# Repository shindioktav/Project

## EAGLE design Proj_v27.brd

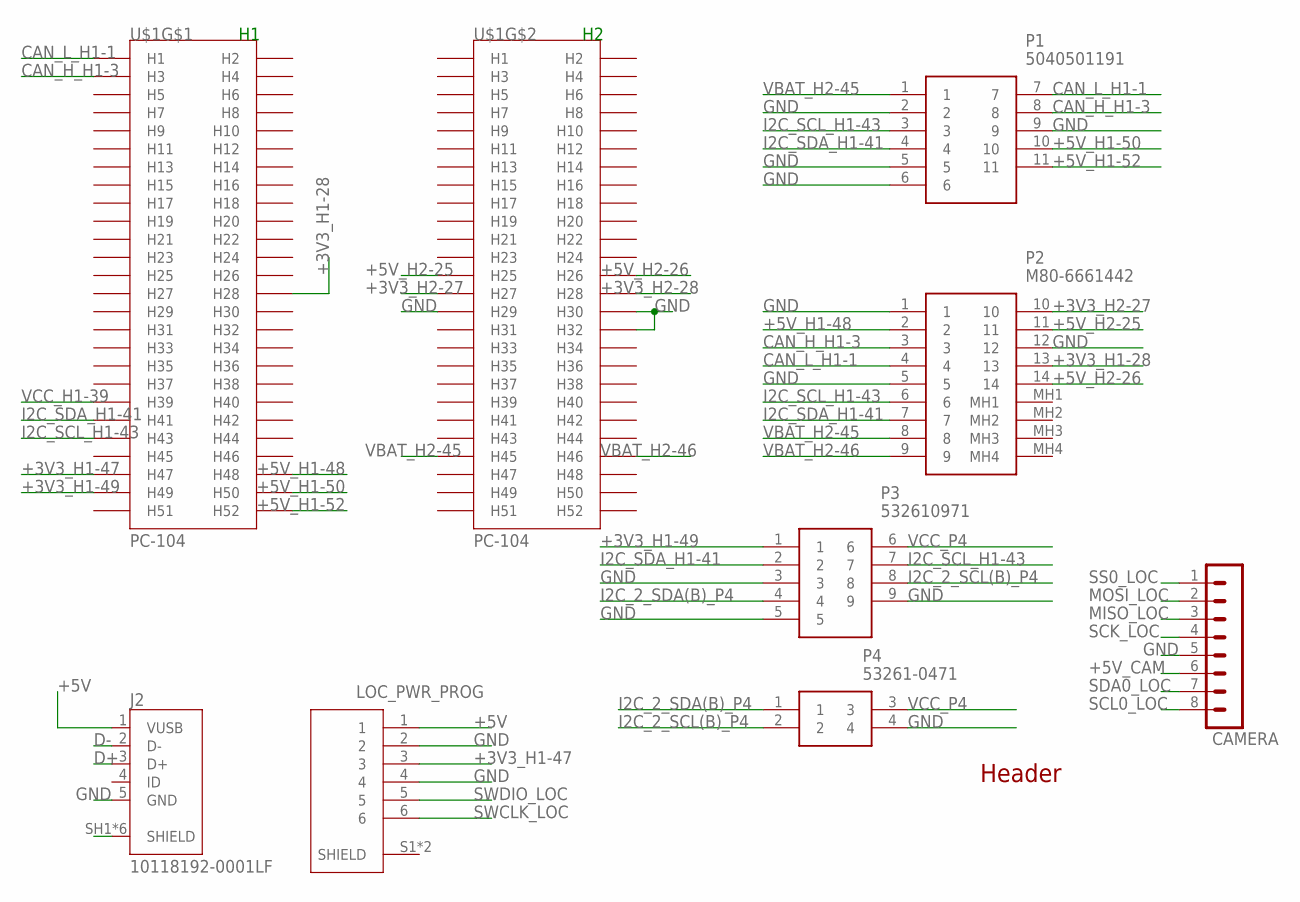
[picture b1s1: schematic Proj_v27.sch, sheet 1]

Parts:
CAMERA: MA08-1
J2: 10118192-0001LF; AMPHENOL_10118192-0001LF
LOC_PWR_PROG: 0532610671; MOLEX_0532610671
P1: 5040501191
P2: M80-6661442; M806661442
P3: 532610971
P4: 53261-0471
U$1: PC-104

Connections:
+3V3_H1-28: P2.13, U$1.P$28 (H28)
+3V3_H1-47: LOC_PWR_PROG.3, U$1.P$47 (H47); also elsewhere on the board
+3V3_H1-49: P3.1, U$1.P$49 (H49)
+3V3_H2-27: P2.10, U$1.P$79 (H27)
+3V3_H2-28: U$1.P$80 (H28)
+5V: J2.1 (VUSB), LOC_PWR_PROG.1; also elsewhere on the board
+5V_CAM: CAMERA.6; also elsewhere on the board
+5V_H1-48: P2.2, U$1.P$48 (H48)
+5V_H1-50: P1.10, U$1.P$50 (H50)
+5V_H1-52: P1.11, U$1.P$52 (H52)
+5V_H2-25: P2.11, U$1.P$77 (H25)
+5V_H2-26: P2.14, U$1.P$78 (H26)
CAN_H_H1-3: P1.8, P2.3, U$1.P$3 (H3)
CAN_L_H1-1: P1.7, P2.4, U$1.P$1 (H1)
D+: J2.3 (D+); also elsewhere on the board
D-: J2.2 (D-); also elsewhere on the board
GND: CAMERA.5, J2.5 (GND), J2.SH1 (SHIELD), J2.SH2 (SHIELD), J2.SH3 (SHIELD), J2.SH4 (SHIELD), J2.SH5 (SHIELD), J2.SH6 (SHIELD), LOC_PWR_PROG.2, LOC_PWR_PROG.4, P1.2, P1.5, P1.6, P1.9, P2.1, P2.5, P2.12, P3.3, P3.5, P3.9, P4.4, U$1.P$81 (H29), U$1.P$82 (H30), U$1.P$84 (H32); also elsewhere on the board
I2C_2_SCL(B)_P4: P3.8, P4.2
I2C_2_SDA(B)_P4: P3.4, P4.1
I2C_SCL_H1-43: P1.3, P2.6, P3.7, U$1.P$43 (H43); also elsewhere on the board
I2C_SDA_H1-41: P1.4, P2.7, P3.2, U$1.P$41 (H41); also elsewhere on the board
MISO_LOC: CAMERA.3; also elsewhere on the board
MOSI_LOC: CAMERA.2; also elsewhere on the board
SCK_LOC: CAMERA.4; also elsewhere on the board
SCL0_LOC: CAMERA.8; also elsewhere on the board
SDA0_LOC: CAMERA.7; also elsewhere on the board
SS0_LOC: CAMERA.1; also elsewhere on the board
SWCLK_LOC: LOC_PWR_PROG.6; also elsewhere on the board
SWDIO_LOC: LOC_PWR_PROG.5; also elsewhere on the board
VBAT_H2-45: P1.1, P2.8, U$1.P$97 (H45)
VBAT_H2-46: P2.9, U$1.P$98 (H46)
VCC_H1-39: U$1.P$39 (H39)
VCC_P4: P3.6, P4.3

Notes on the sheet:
Header

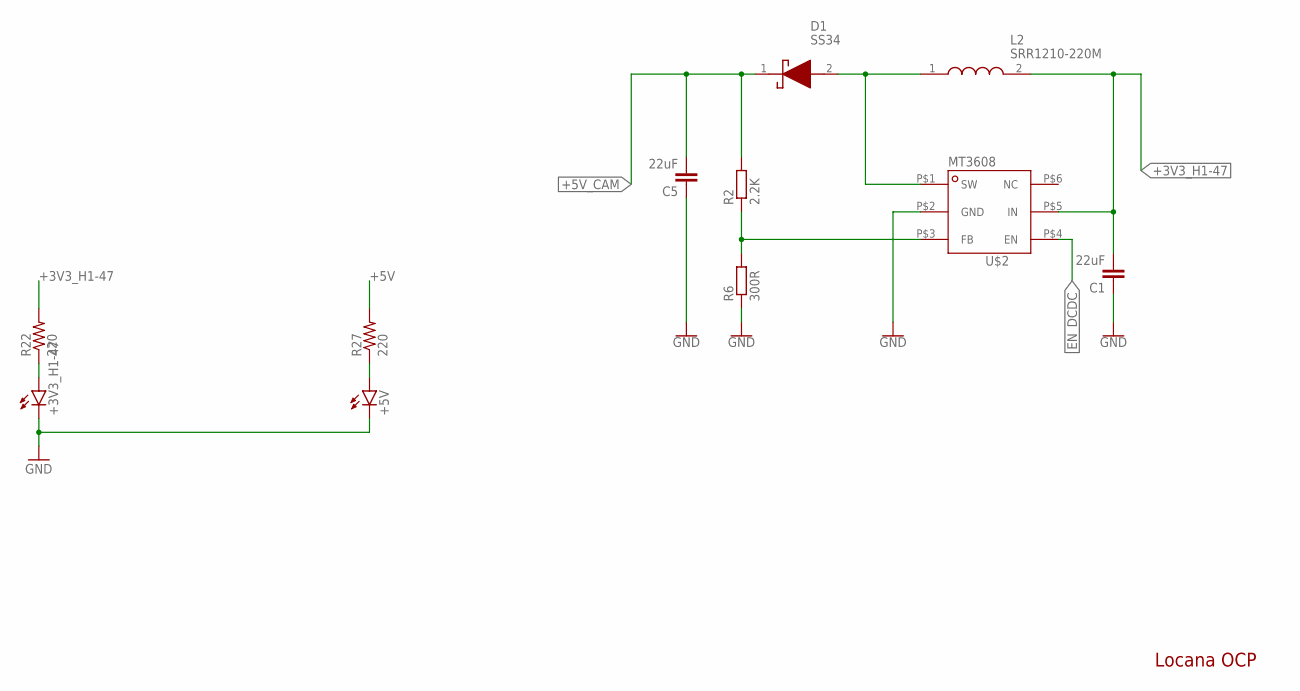
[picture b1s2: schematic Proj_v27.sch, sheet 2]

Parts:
+3V3_H1-47, +5V: LEDCHIP-LED0805; CHIP-LED0805
C1, C5: 22uF; C0805
D1: SS34; DIOM7959X262N
L2: SRR1210-220M; INDPM120120X1000N
R2: 2.2K; M0805
R6: 300R; M0805
R22, R27: 220; M0805
U$2: MT3608SOT23-6; SOT23-6

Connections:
+3V3_H1-47: C1.2, L2.2, R22.2, U$2.P$5 (IN); also elsewhere on the board
+5V: R27.2; also elsewhere on the board
+5V_CAM: C5.2, D1.1 (K), R2.2; also elsewhere on the board
EN_DCDC: U$2.P$4 (EN); also elsewhere on the board
GND: +3V3_H1-47.C, +5V.C, C1.1, C5.1, R6.1, U$2.P$2 (GND); also elsewhere on the board
unnamed: D1.2 (A), L2.1, U$2.P$1 (SW)
unnamed: R2.1, R6.2, U$2.P$3 (FB)
unnamed: +3V3_H1-47.A, R22.1
unnamed: +5V.A, R27.1

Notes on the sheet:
Locana OCP

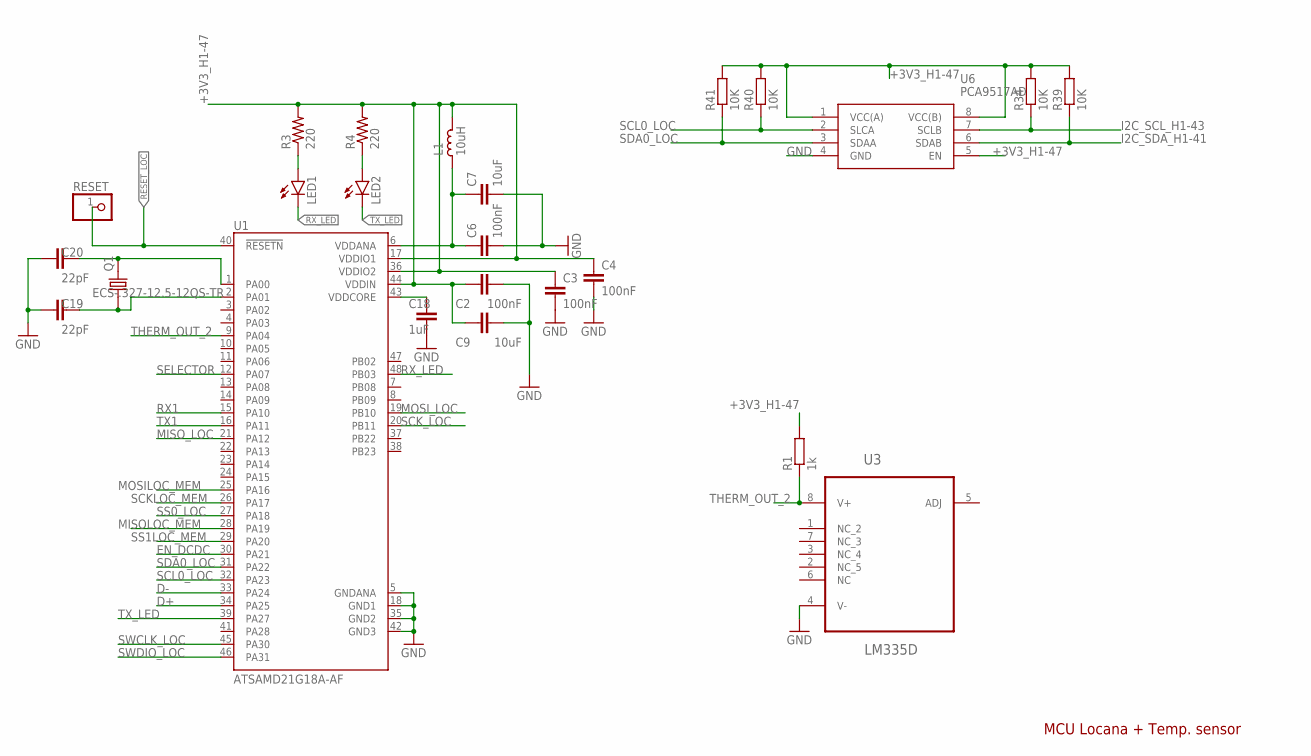
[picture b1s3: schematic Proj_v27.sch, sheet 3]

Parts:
C2, C3, C4, C6: 100nF; C0805K
C7, C9: 10uF; C0805K
C18: 1uF; C0805K
C19, C20: 22pF; C0805K
L1: 10uH; L0805
LED1, LED2: LEDCHIP-LED0805; CHIP-LED0805
Q1: ECS-.327-12.5-12QS-TR; XTAL_ECS-.327-12.5-12QS-TR
R1: 1k; M0805
R3, R4: 220; M0805
R34, R39, R40, R41: 10K; M0805
RESET: PINHD-1X1; 1X01
U1: ATSAMD21G18A-AF; QFP50P900X900X120-48N
U3: LM335D; SOIC127P600X175-8N
U6: PCA9517AD; SOIC127P600X175-8N

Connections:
+3V3_H1-47: C2.1, C3.1, C4.1, C9.1, L1.1, R1.2, R3.2, R4.2, R34.2, R39.2, R40.2, R41.2, U1.17 (VDDIO1), U1.36 (VDDIO2), U1.44 (VDDIN), U6.1 (VCC(A)), U6.5 (EN), U6.8 (VCC(B)); also elsewhere on the board
D+: U1.34 (PA25); also elsewhere on the board
D-: U1.33 (PA24); also elsewhere on the board
EN_DCDC: U1.30 (PA21); also elsewhere on the board
GND: C2.2, C3.2, C4.2, C6.2, C7.2, C9.2, C18.2, C19.1, C20.1, U1.5 (GNDANA), U1.18 (GND1), U1.35 (GND2), U1.42 (GND3), U3.4 (V-), U6.4 (GND); also elsewhere on the board
I2C_SCL_H1-43: R34.1, U6.7 (SCLB); also elsewhere on the board
I2C_SDA_H1-41: R39.1, U6.6 (SDAB); also elsewhere on the board
MISOLOC_MEM: U1.28 (PA19); also elsewhere on the board
MISO_LOC: U1.21 (PA12); also elsewhere on the board
MOSILOC_MEM: U1.25 (PA16); also elsewhere on the board
MOSI_LOC: U1.19 (PB10); also elsewhere on the board
unnamed: C20.2, Q1.2, U1.1 (PA00)
unnamed: C6.1, C7.1, L1.2, U1.6 (VDDANA)
unnamed: LED1.A, R3.1
unnamed: C18.1, U1.43 (VDDCORE)
unnamed: C19.2, Q1.1, U1.2 (PA01)
unnamed: LED2.A, R4.1
RESET_LOC: RESET.1, U1.40 (!RESETN)
RX1: U1.15 (PA10); also elsewhere on the board
RX_LED: LED1.C, U1.48 (PB03)
SCKLOC_MEM: U1.26 (PA17); also elsewhere on the board
SCK_LOC: U1.20 (PB11); also elsewhere on the board
SCL0_LOC: R40.1, U1.32 (PA23), U6.2 (SLCA); also elsewhere on the board
SDA0_LOC: R41.1, U1.31 (PA22), U6.3 (SDAA); also elsewhere on the board
SELECTOR: U1.12 (PA07); also elsewhere on the board
SS0_LOC: U1.27 (PA18); also elsewhere on the board
SS1LOC_MEM: U1.29 (PA20); also elsewhere on the board
SWCLK_LOC: U1.45 (PA30); also elsewhere on the board
SWDIO_LOC: U1.46 (PA31); also elsewhere on the board
THERM_OUT_2: R1.1, U1.9 (PA04), U3.8 (V+)
TX1: U1.16 (PA11); also elsewhere on the board
TX_LED: LED2.C, U1.39 (PA27)

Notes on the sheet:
MCU Locana + Temp. sensor

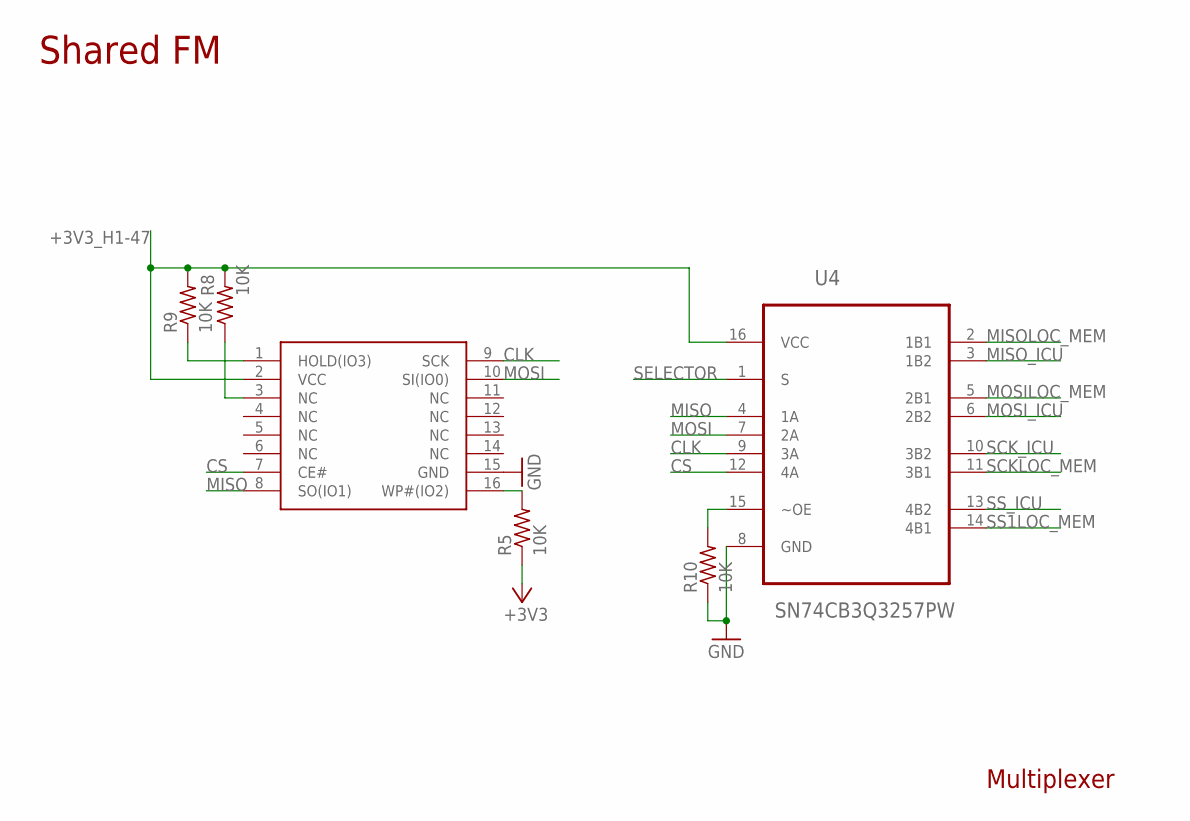
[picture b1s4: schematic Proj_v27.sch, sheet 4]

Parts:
LOC_MEM: SOIC127P600X175-16NSOIC-16YAS; SOIC127P1032X265-17T480X861N
R5, R8, R9, R10: 10K; M0805
U4: SN74CB3Q3257PW; SOP65P640X120-16N

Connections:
+3V3_H1-47: LOC_MEM.2 (VCC), R5.1, R8.2, R9.2, U4.16 (VCC); also elsewhere on the board
CLK: LOC_MEM.9 (SCK), U4.9 (3A)
CS: LOC_MEM.7 (CE#), U4.12 (4A)
GND: LOC_MEM.15 (GND), R10.1, U4.8 (GND); also elsewhere on the board
MISO: LOC_MEM.8 (SO(IO1)), U4.4 (1A)
MISOLOC_MEM: U4.2 (1B1); also elsewhere on the board
MISO_ICU: U4.3 (1B2); also elsewhere on the board
MOSI: LOC_MEM.10 (SI(IO0)), U4.7 (2A)
MOSILOC_MEM: U4.5 (2B1); also elsewhere on the board
MOSI_ICU: U4.6 (2B2); also elsewhere on the board
unnamed: LOC_MEM.16 (WP#(IO2)), R5.2
unnamed: LOC_MEM.1 (HOLD(IO3)), R9.1
unnamed: LOC_MEM.3 (NC), R8.1
unnamed: R10.2, U4.15 (~OE)
SCKLOC_MEM: U4.11 (3B1); also elsewhere on the board
SCK_ICU: U4.10 (3B2); also elsewhere on the board
SELECTOR: U4.1 (S); also elsewhere on the board
SS1LOC_MEM: U4.14 (4B1); also elsewhere on the board
SS_ICU: U4.13 (4B2); also elsewhere on the board

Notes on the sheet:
Shared FM
Multiplexer

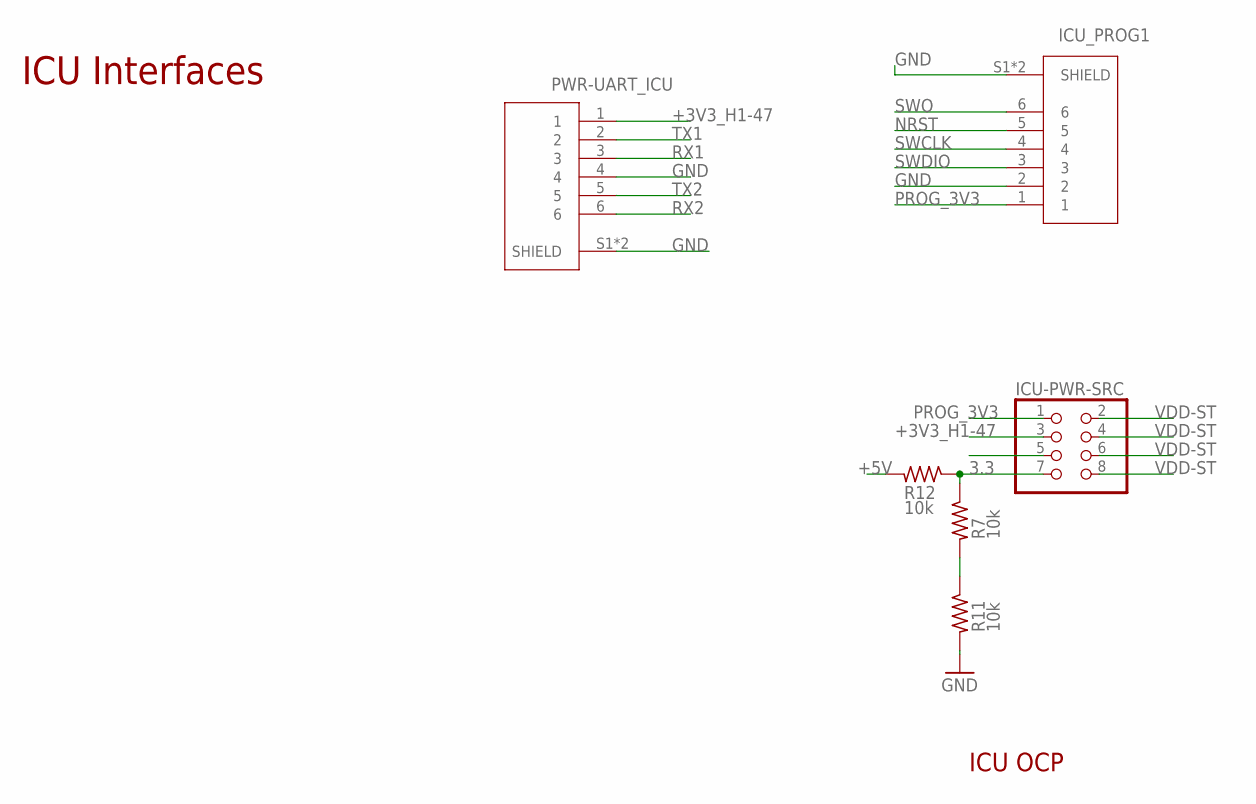
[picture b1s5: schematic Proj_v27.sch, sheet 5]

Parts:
ICU-PWR-SRC: PINHD-2X4; 2X04
ICU_PROG1: 0532610671; MOLEX_0532610671
PWR-UART_ICU: 0532610671; MOLEX_0532610671
R7, R11, R12: 10k; R0805

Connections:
3.3: ICU-PWR-SRC.7, R7.1, R12.1
+3V3_H1-47: ICU-PWR-SRC.3, PWR-UART_ICU.1; also elsewhere on the board
+5V: R12.2; also elsewhere on the board
GND: ICU_PROG1.2, ICU_PROG1.S1 (SHIELD), ICU_PROG1.S2 (SHIELD), PWR-UART_ICU.4, PWR-UART_ICU.S1 (SHIELD), PWR-UART_ICU.S2 (SHIELD), R11.2; also elsewhere on the board
unnamed: R7.2, R11.1
NRST: ICU_PROG1.5; also elsewhere on the board
PROG_3V3: ICU-PWR-SRC.1, ICU_PROG1.1
RX1: PWR-UART_ICU.3; also elsewhere on the board
RX2: PWR-UART_ICU.6; also elsewhere on the board
SWCLK: ICU_PROG1.4; also elsewhere on the board
SWDIO: ICU_PROG1.3; also elsewhere on the board
SWO: ICU_PROG1.6; also elsewhere on the board
TX1: PWR-UART_ICU.2; also elsewhere on the board
TX2: PWR-UART_ICU.5; also elsewhere on the board
VDD-ST: ICU-PWR-SRC.2, ICU-PWR-SRC.4, ICU-PWR-SRC.6, ICU-PWR-SRC.8; also elsewhere on the board

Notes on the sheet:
ICU Interfaces
ICU OCP

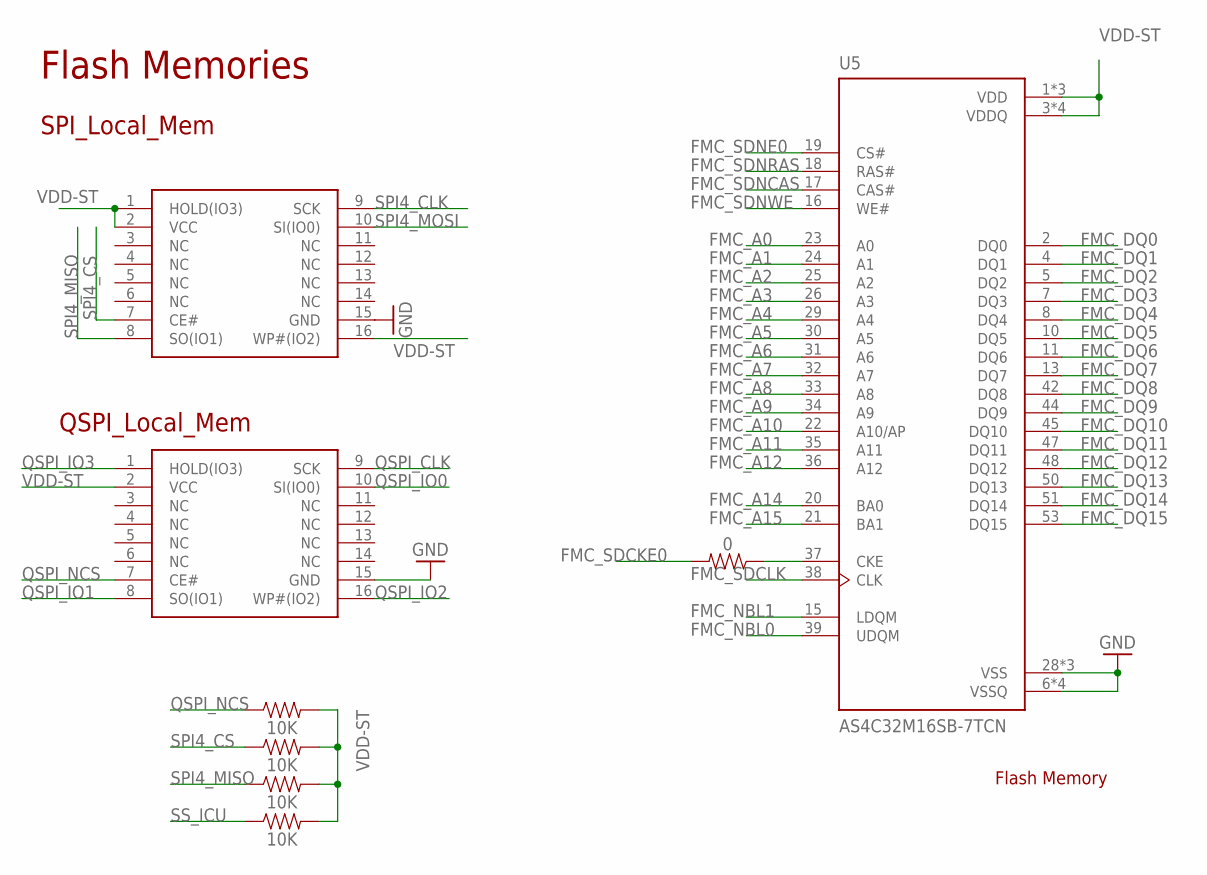
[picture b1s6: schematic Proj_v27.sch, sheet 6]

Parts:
LOCAL_MEM: SOIC127P600X175-16NSOIC-16YAS; SOIC127P1032X265-17T480X861N
QSPI_MEM: SOIC127P600X175-16NSOIC-16YAS; SOIC127P1032X265-17T480X861N
R25: 0; R0805
R76, R77, R78, R79: 10K; R0805
U5: AS4C32M16SB-7TCN; SOP80P1176X120-54N

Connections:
FMC_A0: U5.23 (A0); also elsewhere on the board
FMC_A1: U5.24 (A1); also elsewhere on the board
FMC_A2: U5.25 (A2); also elsewhere on the board
FMC_A3: U5.26 (A3); also elsewhere on the board
FMC_A4: U5.29 (A4); also elsewhere on the board
FMC_A5: U5.30 (A5); also elsewhere on the board
FMC_A6: U5.31 (A6); also elsewhere on the board
FMC_A7: U5.32 (A7); also elsewhere on the board
FMC_A8: U5.33 (A8); also elsewhere on the board
FMC_A9: U5.34 (A9); also elsewhere on the board
FMC_A10: U5.22 (A10/AP); also elsewhere on the board
FMC_A11: U5.35 (A11); also elsewhere on the board
FMC_A12: U5.36 (A12); also elsewhere on the board
FMC_A14: U5.20 (BA0); also elsewhere on the board
FMC_A15: U5.21 (BA1); also elsewhere on the board
FMC_DQ0: U5.2 (DQ0); also elsewhere on the board
FMC_DQ1: U5.4 (DQ1); also elsewhere on the board
FMC_DQ2: U5.5 (DQ2); also elsewhere on the board
FMC_DQ3: U5.7 (DQ3); also elsewhere on the board
FMC_DQ4: U5.8 (DQ4); also elsewhere on the board
FMC_DQ5: U5.10 (DQ5); also elsewhere on the board
FMC_DQ6: U5.11 (DQ6); also elsewhere on the board
FMC_DQ7: U5.13 (DQ7); also elsewhere on the board
FMC_DQ8: U5.42 (DQ8); also elsewhere on the board
FMC_DQ9: U5.44 (DQ9); also elsewhere on the board
FMC_DQ10: U5.45 (DQ10); also elsewhere on the board
FMC_DQ11: U5.47 (DQ11); also elsewhere on the board
FMC_DQ12: U5.48 (DQ12); also elsewhere on the board
FMC_DQ13: U5.50 (DQ13); also elsewhere on the board
FMC_DQ14: U5.51 (DQ14); also elsewhere on the board
FMC_DQ15: U5.53 (DQ15); also elsewhere on the board
FMC_NBL0: U5.39 (UDQM); also elsewhere on the board
FMC_NBL1: U5.15 (LDQM); also elsewhere on the board
FMC_SDCKE0: R25.1, R25.2, U5.37 (CKE); also elsewhere on the board
FMC_SDCLK: U5.38 (CLK); also elsewhere on the board
FMC_SDNCAS: U5.17 (CAS#); also elsewhere on the board
FMC_SDNE0: U5.19 (CS#); also elsewhere on the board
FMC_SDNRAS: U5.18 (RAS#); also elsewhere on the board
FMC_SDNWE: U5.16 (WE#); also elsewhere on the board
GND: LOCAL_MEM.15 (GND), QSPI_MEM.15 (GND), U5.6 (VSSQ), U5.12 (VSSQ), U5.28 (VSS), U5.41 (VSS), U5.46 (VSSQ), U5.52 (VSSQ), U5.54 (VSS); also elsewhere on the board
QSPI_CLK: QSPI_MEM.9 (SCK); also elsewhere on the board
QSPI_IO0: QSPI_MEM.10 (SI(IO0)); also elsewhere on the board
QSPI_IO1: QSPI_MEM.8 (SO(IO1)); also elsewhere on the board
QSPI_IO2: QSPI_MEM.16 (WP#(IO2)); also elsewhere on the board
QSPI_IO3: QSPI_MEM.1 (HOLD(IO3)); also elsewhere on the board
QSPI_NCS: QSPI_MEM.7 (CE#), R79.1; also elsewhere on the board
SPI4_CLK: LOCAL_MEM.9 (SCK); also elsewhere on the board
SPI4_CS: LOCAL_MEM.7 (CE#), R78.1; also elsewhere on the board
SPI4_MISO: LOCAL_MEM.8 (SO(IO1)), R77.1; also elsewhere on the board
SPI4_MOSI: LOCAL_MEM.10 (SI(IO0)); also elsewhere on the board
SS_ICU: R76.1; also elsewhere on the board
VDD-ST: LOCAL_MEM.1 (HOLD(IO3)), LOCAL_MEM.2 (VCC), LOCAL_MEM.16 (WP#(IO2)), QSPI_MEM.2 (VCC), R76.2, R77.2, R78.2, R79.2, U5.1 (VDD), U5.3 (VDDQ), U5.9 (VDDQ), U5.14 (VDD), U5.27 (VDD), U5.43 (VDDQ), U5.49 (VDDQ); also elsewhere on the board

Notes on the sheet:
Flash Memories
SPI_Local_Mem
Flash Memory
QSPI_Local_Mem

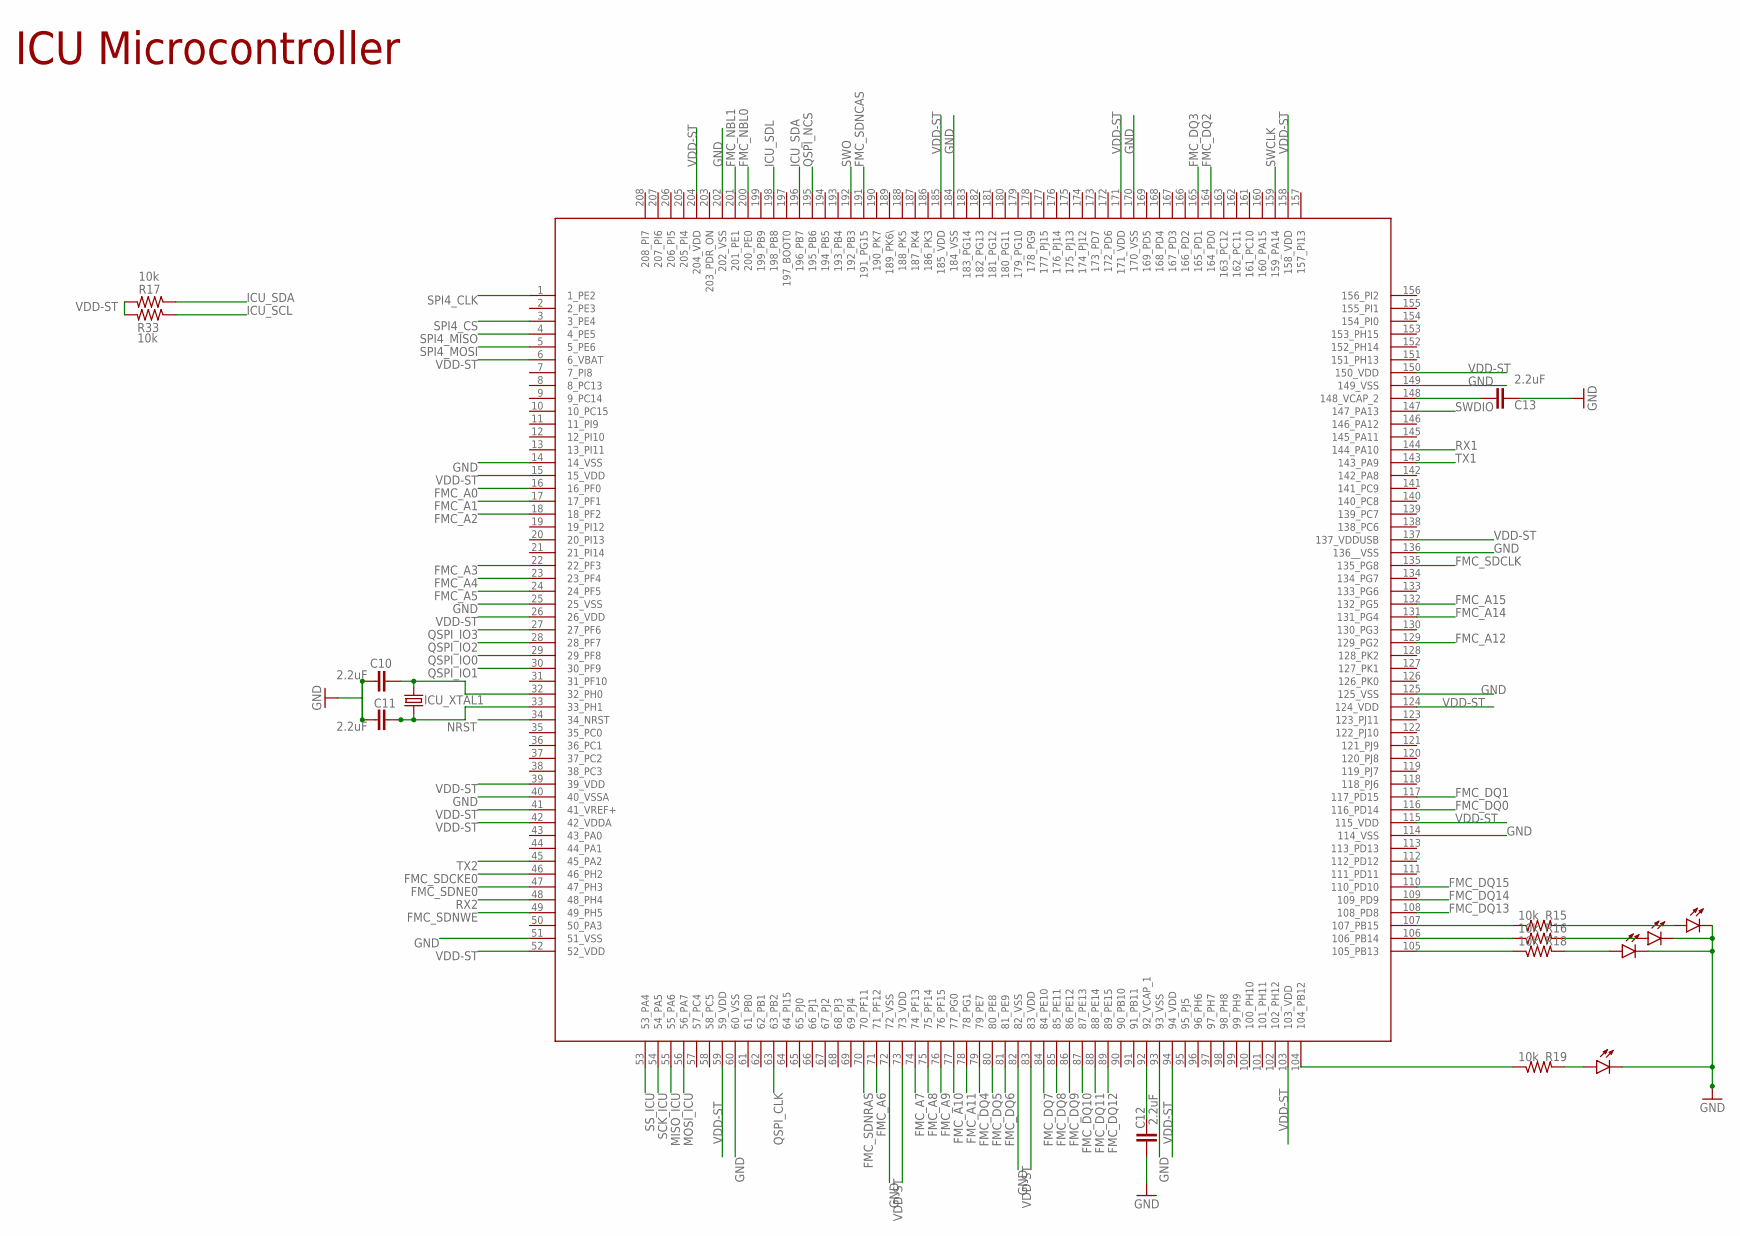
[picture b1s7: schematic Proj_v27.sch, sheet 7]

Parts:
C10, C11, C12, C13: 2.2uF; C0805
ICU_XTAL1: CRYSTALHC49UP; HC49UP
L07, L08, L09, L10: LEDCHIPLED_0805; CHIPLED_0805
R15, R16, R17, R18, R19, R33: 10k; R0805
STM32F7646BGT6: STM32F746BGT6; QFP50P3000X3000X160-208N

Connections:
FMC_A0: STM32F7646BGT6.16 (16_PF0); also elsewhere on the board
FMC_A1: STM32F7646BGT6.17 (17_PF1); also elsewhere on the board
FMC_A2: STM32F7646BGT6.18 (18_PF2); also elsewhere on the board
FMC_A3: STM32F7646BGT6.22 (22_PF3); also elsewhere on the board
FMC_A4: STM32F7646BGT6.23 (23_PF4); also elsewhere on the board
FMC_A5: STM32F7646BGT6.24 (24_PF5); also elsewhere on the board
FMC_A6: STM32F7646BGT6.71 (71_PF12); also elsewhere on the board
FMC_A7: STM32F7646BGT6.74 (74_PF13); also elsewhere on the board
FMC_A8: STM32F7646BGT6.75 (75_PF14); also elsewhere on the board
FMC_A9: STM32F7646BGT6.76 (76_PF15); also elsewhere on the board
FMC_A10: STM32F7646BGT6.77 (77_PG0); also elsewhere on the board
FMC_A11: STM32F7646BGT6.78 (78_PG1); also elsewhere on the board
FMC_A12: STM32F7646BGT6.129 (129_PG2); also elsewhere on the board
FMC_A14: STM32F7646BGT6.131 (131_PG4); also elsewhere on the board
FMC_A15: STM32F7646BGT6.132 (132_PG5); also elsewhere on the board
FMC_DQ0: STM32F7646BGT6.116 (116_PD14); also elsewhere on the board
FMC_DQ1: STM32F7646BGT6.117 (117_PD15); also elsewhere on the board
FMC_DQ2: STM32F7646BGT6.164 (164_PD0); also elsewhere on the board
FMC_DQ3: STM32F7646BGT6.165 (165_PD1); also elsewhere on the board
FMC_DQ4: STM32F7646BGT6.79 (79_PE7); also elsewhere on the board
FMC_DQ5: STM32F7646BGT6.80 (80_PE8); also elsewhere on the board
FMC_DQ6: STM32F7646BGT6.81 (81_PE9); also elsewhere on the board
FMC_DQ7: STM32F7646BGT6.84 (84_PE10); also elsewhere on the board
FMC_DQ8: STM32F7646BGT6.85 (85_PE11); also elsewhere on the board
FMC_DQ9: STM32F7646BGT6.86 (86_PE12); also elsewhere on the board
FMC_DQ10: STM32F7646BGT6.87 (87_PE13); also elsewhere on the board
FMC_DQ11: STM32F7646BGT6.88 (88_PE14); also elsewhere on the board
FMC_DQ12: STM32F7646BGT6.89 (89_PE15); also elsewhere on the board
FMC_DQ13: STM32F7646BGT6.108 (108_PD8); also elsewhere on the board
FMC_DQ14: STM32F7646BGT6.109 (109_PD9); also elsewhere on the board
FMC_DQ15: STM32F7646BGT6.110 (110_PD10); also elsewhere on the board
FMC_NBL0: STM32F7646BGT6.200 (200_PE0); also elsewhere on the board
FMC_NBL1: STM32F7646BGT6.201 (201_PE1); also elsewhere on the board
FMC_SDCKE0: STM32F7646BGT6.46 (46_PH2); also elsewhere on the board
FMC_SDCLK: STM32F7646BGT6.135 (135_PG8); also elsewhere on the board
FMC_SDNCAS: STM32F7646BGT6.191 (191_PG15); also elsewhere on the board
FMC_SDNE0: STM32F7646BGT6.47 (47_PH3); also elsewhere on the board
FMC_SDNRAS: STM32F7646BGT6.70 (70_PF11); also elsewhere on the board
FMC_SDNWE: STM32F7646BGT6.49 (49_PH5); also elsewhere on the board
GND: C10.1, C11.1, C12.1, C13.1, L07.C, L08.C, L09.C, L10.C, STM32F7646BGT6.14 (14_VSS), STM32F7646BGT6.25 (25_VSS), STM32F7646BGT6.40 (40_VSSA), STM32F7646BGT6.51 (51_VSS), STM32F7646BGT6.60 (60_VSS), STM32F7646BGT6.72 (72_VSS), STM32F7646BGT6.82 (82_VSS), STM32F7646BGT6.93 (93_VSS), STM32F7646BGT6.114 (114_VSS), STM32F7646BGT6.125 (125_VSS), STM32F7646BGT6.136 (136__VSS), STM32F7646BGT6.149 (149_VSS), STM32F7646BGT6.170 (170_VSS), STM32F7646BGT6.184 (184_VSS), STM32F7646BGT6.202 (202_VSS); also elsewhere on the board
ICU_SCL: R33.1
ICU_SDA: R17.1, STM32F7646BGT6.196 (196_PB7)
ICU_SDL: STM32F7646BGT6.198 (198_PB8)
L06: L09.A, R18.2
L07: L10.A, R19.2
L08: L07.A, R15.2
L09: L08.A, R16.2
MISO_ICU: STM32F7646BGT6.55 (55_PA6); also elsewhere on the board
MOSI_ICU: STM32F7646BGT6.56 (56_PA7); also elsewhere on the board
unnamed: R19.1, STM32F7646BGT6.104 (104_PB12)
unnamed: R15.1, STM32F7646BGT6.107 (107_PB15)
unnamed: R16.1, STM32F7646BGT6.106 (106_PB14)
unnamed: R18.1, STM32F7646BGT6.105 (105_PB13)
unnamed: C10.2, ICU_XTAL1.2, STM32F7646BGT6.32 (32_PH0)
unnamed: C12.2, STM32F7646BGT6.92 (92_VCAP_1)
unnamed: C13.2, STM32F7646BGT6.148 (148_VCAP_2)
NRST: STM32F7646BGT6.34 (34_NRST); also elsewhere on the board
QSPI_CLK: STM32F7646BGT6.63 (63_PB2); also elsewhere on the board
QSPI_IO0: STM32F7646BGT6.29 (29_PF8); also elsewhere on the board
QSPI_IO1: STM32F7646BGT6.30 (30_PF9); also elsewhere on the board
QSPI_IO2: STM32F7646BGT6.28 (28_PF7); also elsewhere on the board
QSPI_IO3: STM32F7646BGT6.27 (27_PF6); also elsewhere on the board
QSPI_NCS: STM32F7646BGT6.195 (195_PB6); also elsewhere on the board
RX1: STM32F7646BGT6.144 (144_PA10); also elsewhere on the board
RX2: STM32F7646BGT6.48 (48_PH4); also elsewhere on the board
SCK_ICU: STM32F7646BGT6.54 (54_PA5); also elsewhere on the board
SPI4_CLK: STM32F7646BGT6.1 (1_PE2); also elsewhere on the board
SPI4_CS: STM32F7646BGT6.3 (3_PE4); also elsewhere on the board
SPI4_MISO: STM32F7646BGT6.4 (4_PE5); also elsewhere on the board
SPI4_MOSI: STM32F7646BGT6.5 (5_PE6); also elsewhere on the board
SS_ICU: STM32F7646BGT6.53 (53_PA4); also elsewhere on the board
SWCLK: STM32F7646BGT6.159 (159_PA14); also elsewhere on the board
SWDIO: STM32F7646BGT6.147 (147_PA13); also elsewhere on the board
SWO: STM32F7646BGT6.192 (192_PB3); also elsewhere on the board
TX1: STM32F7646BGT6.143 (143_PA9); also elsewhere on the board
TX2: STM32F7646BGT6.45 (45_PA2); also elsewhere on the board
VDD-ST: R17.2, R33.2, STM32F7646BGT6.6 (6_VBAT), STM32F7646BGT6.15 (15_VDD), STM32F7646BGT6.26 (26_VDD), STM32F7646BGT6.39 (39_VDD), STM32F7646BGT6.41 (41_VREF+), STM32F7646BGT6.42 (42_VDDA), STM32F7646BGT6.52 (52_VDD), STM32F7646BGT6.59 (59_VDD), STM32F7646BGT6.73 (73_VDD), STM32F7646BGT6.83 (83_VDD), STM32F7646BGT6.94 (94_VDD), STM32F7646BGT6.103 (103_VDD), STM32F7646BGT6.115 (115_VDD), STM32F7646BGT6.124 (124_VDD), STM32F7646BGT6.137 (137_VDDUSB), STM32F7646BGT6.150 (150_VDD), STM32F7646BGT6.158 (158_VDD), STM32F7646BGT6.171 (171_VDD), STM32F7646BGT6.185 (185_VDD), STM32F7646BGT6.204 (204_VDD); also elsewhere on the board
XTAL4: C11.2, ICU_XTAL1.1, STM32F7646BGT6.33 (33_PH1)

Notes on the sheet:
ICU Microcontroller

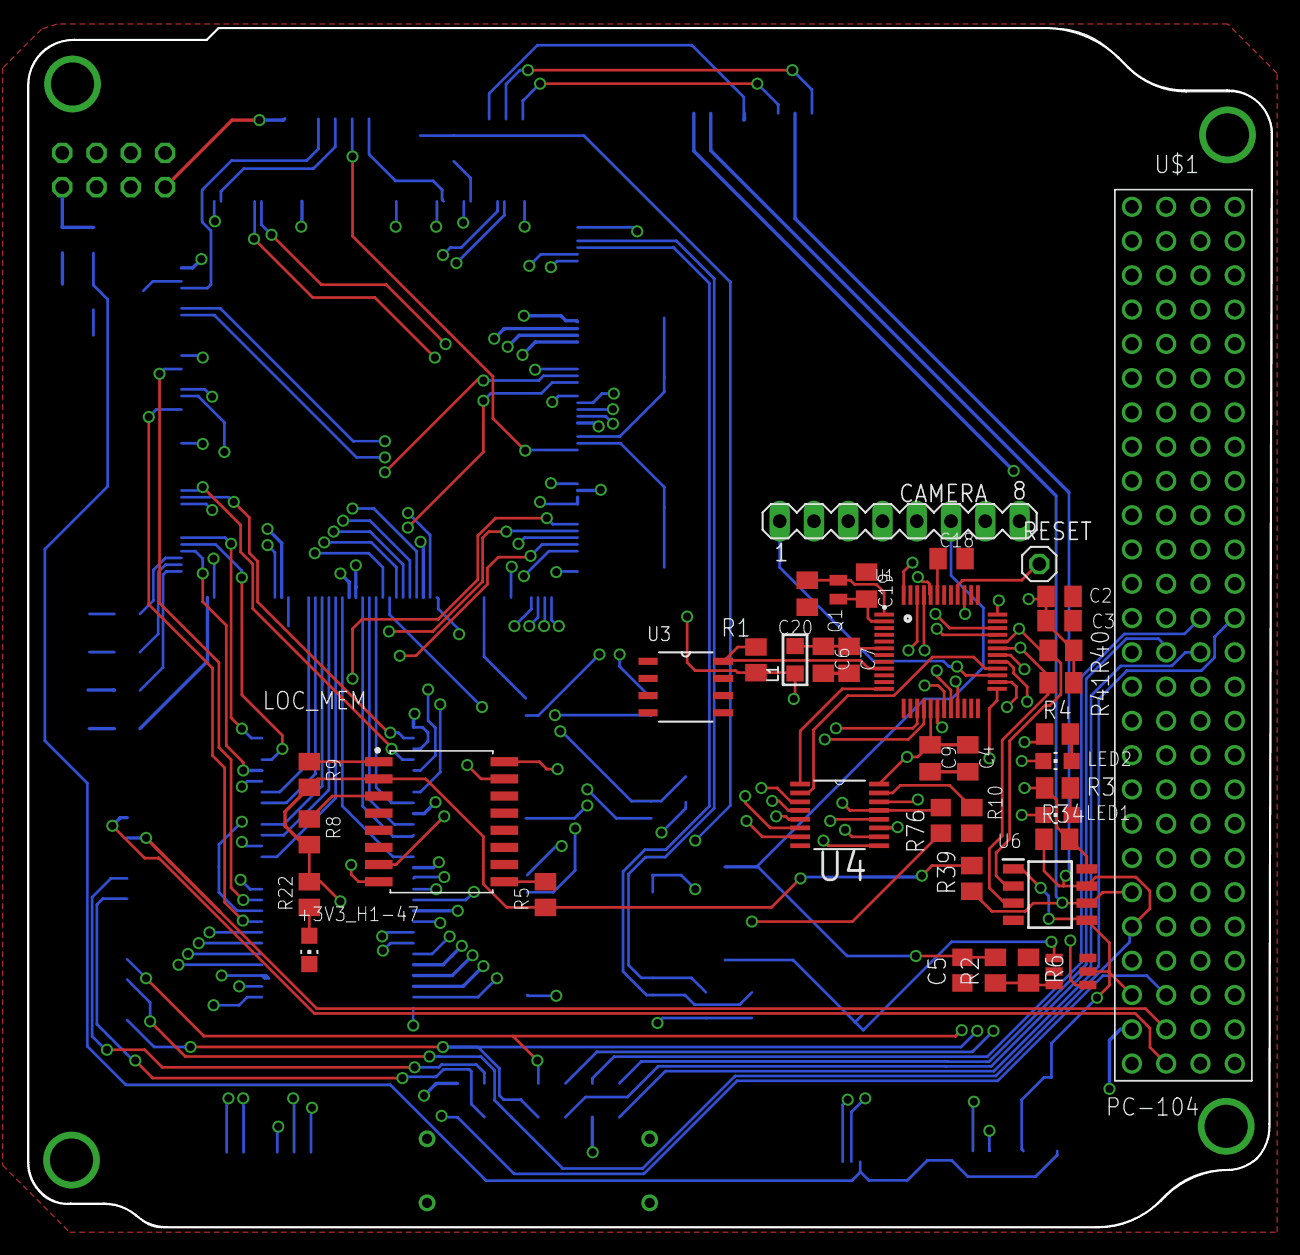
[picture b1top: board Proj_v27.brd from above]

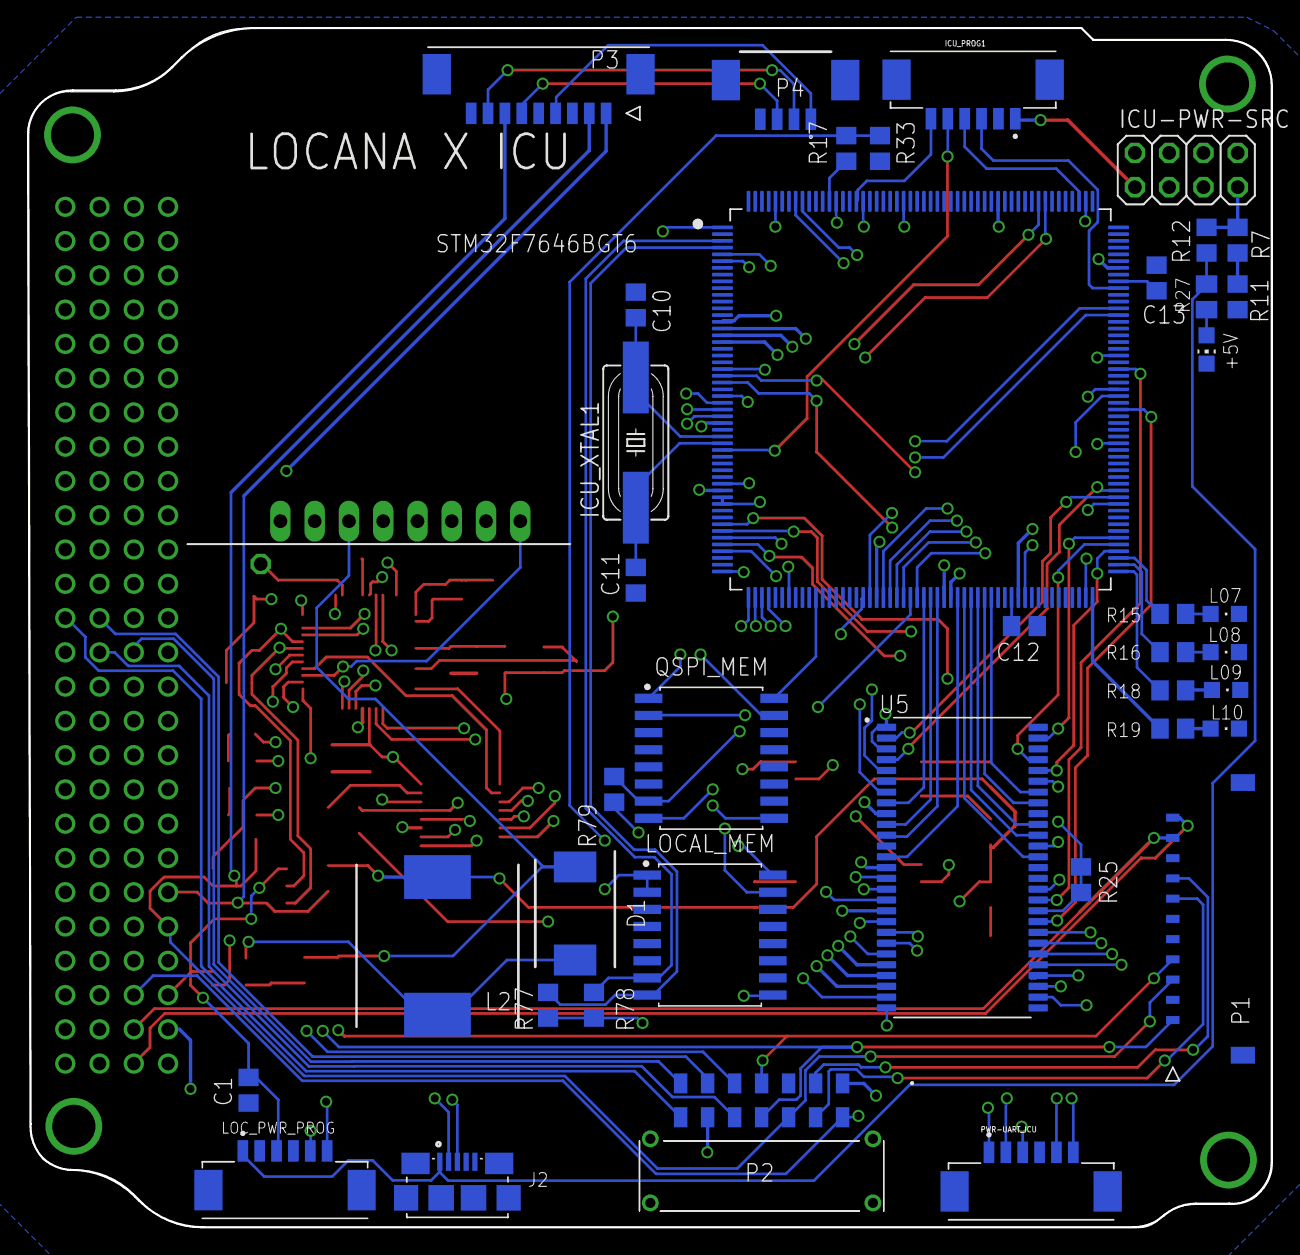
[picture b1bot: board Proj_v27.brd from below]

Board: 4 copper layers, 92.2 x 88.9 mm, 79 parts (40 on the bottom side), 137 nets.

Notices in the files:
parts and their libraries:
rc-master-smd: Copyright (C) 2007, Bob Starr
SparkFun-PowerSymbols: Licensing: Creative Commons ShareAlike 4.0 International - https://creativecommons.org/licenses/by-sa/4.0
